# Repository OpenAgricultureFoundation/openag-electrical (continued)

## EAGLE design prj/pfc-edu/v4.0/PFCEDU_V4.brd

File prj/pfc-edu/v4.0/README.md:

## Electrical Design

Files here can be delivered to a contract manufacturer for PCB production. 

- BOM
- Gerber files
- PCB schematic (Eagle)
- PCB board (Eagle)

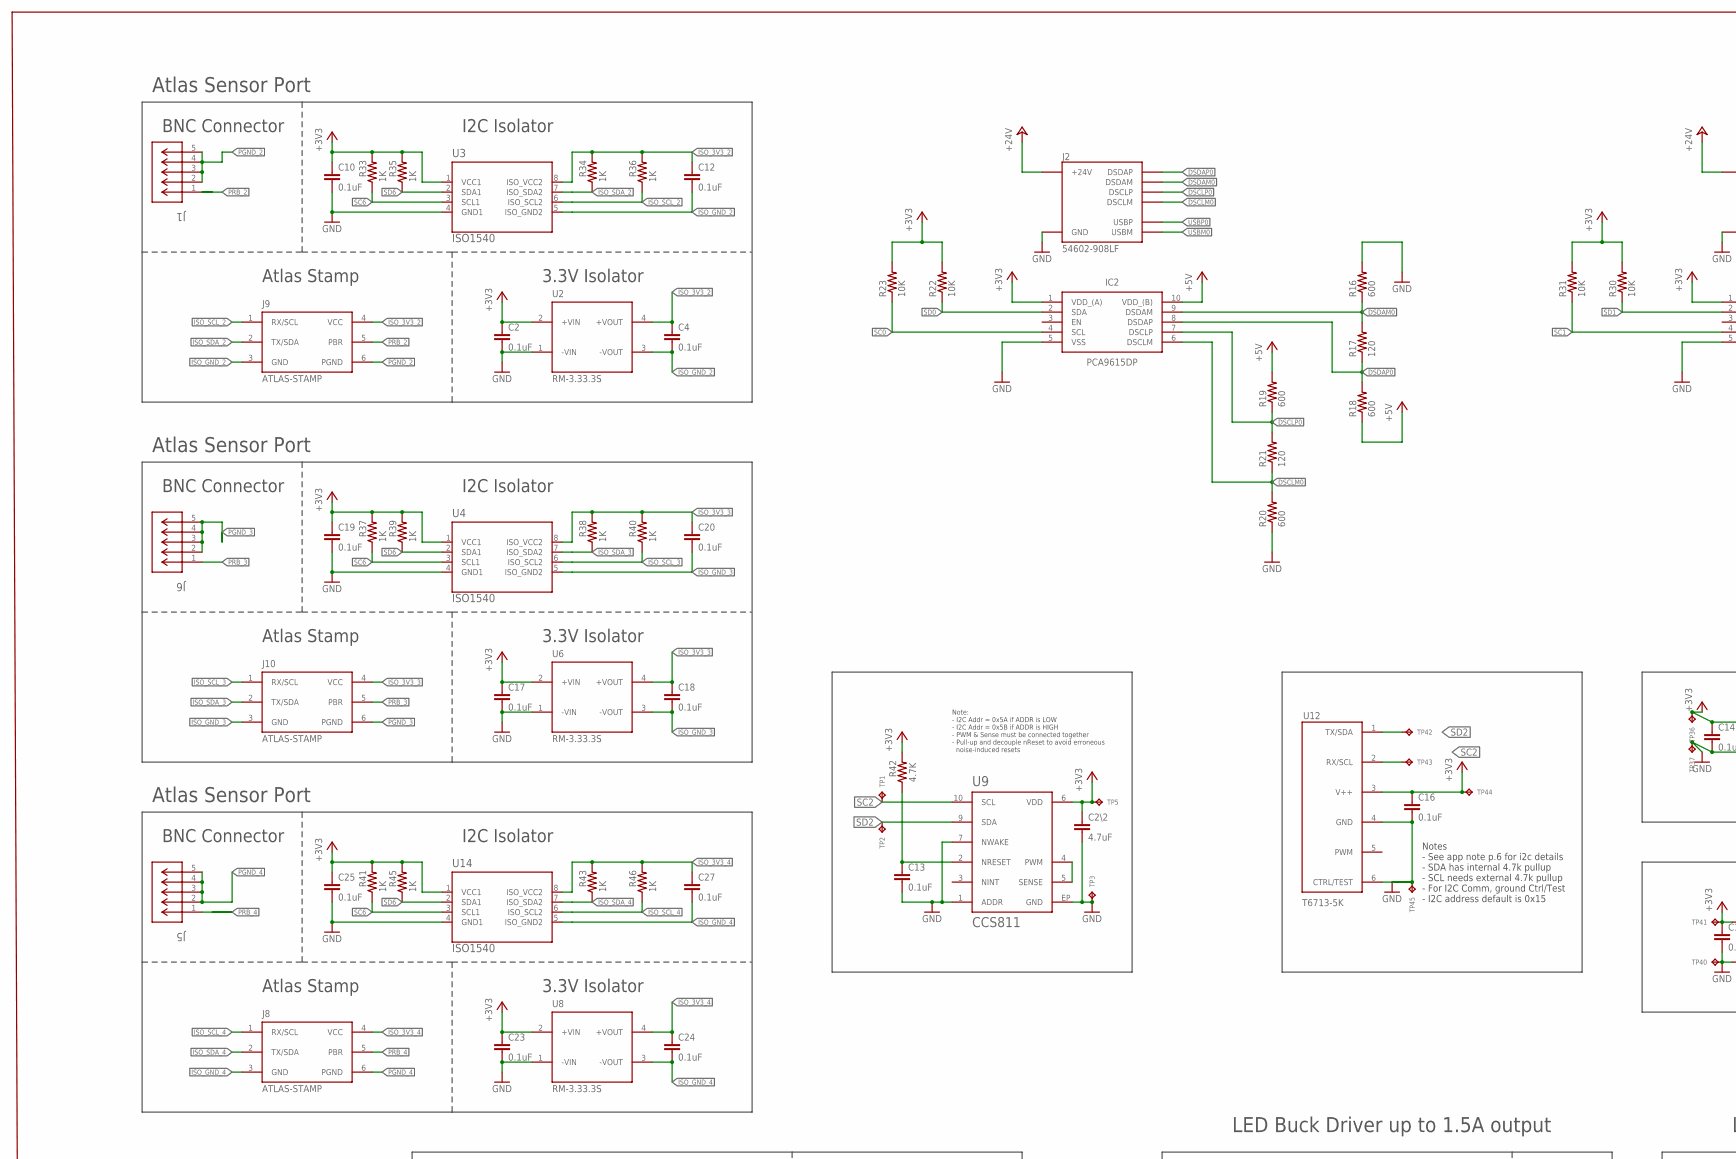
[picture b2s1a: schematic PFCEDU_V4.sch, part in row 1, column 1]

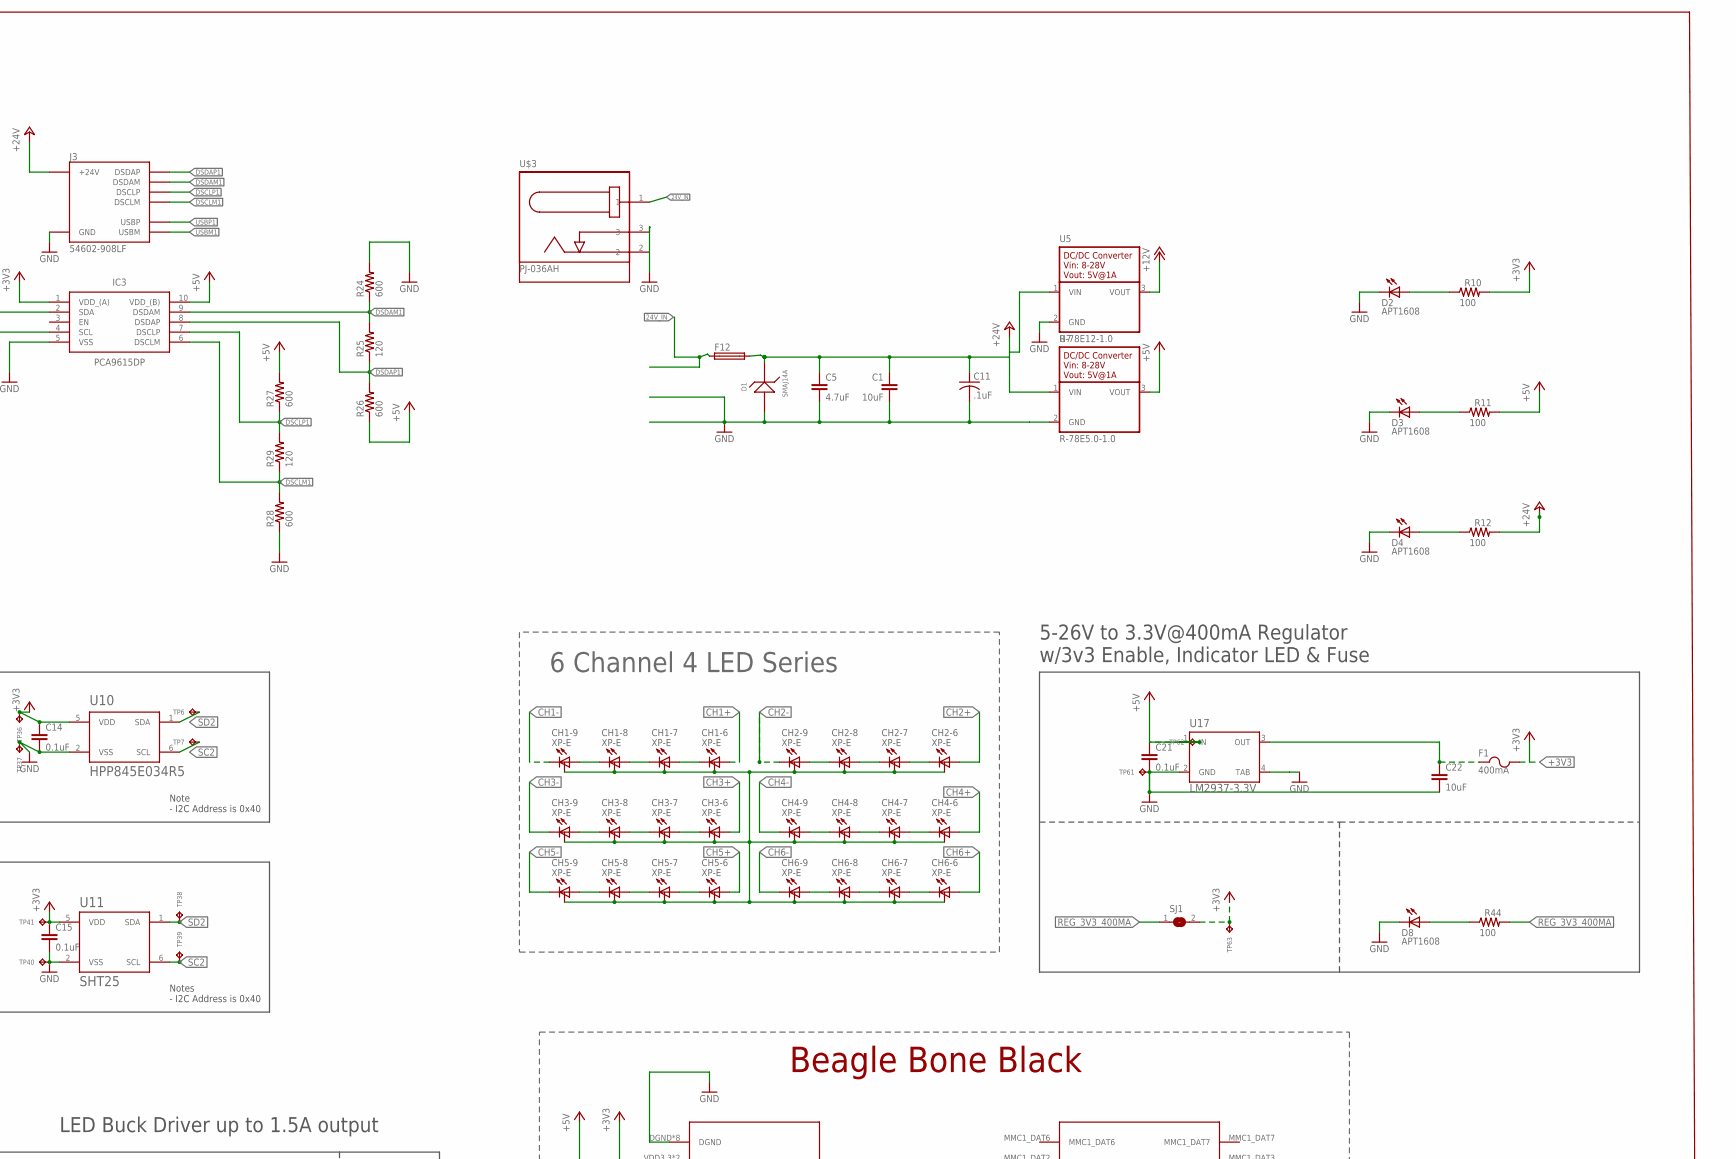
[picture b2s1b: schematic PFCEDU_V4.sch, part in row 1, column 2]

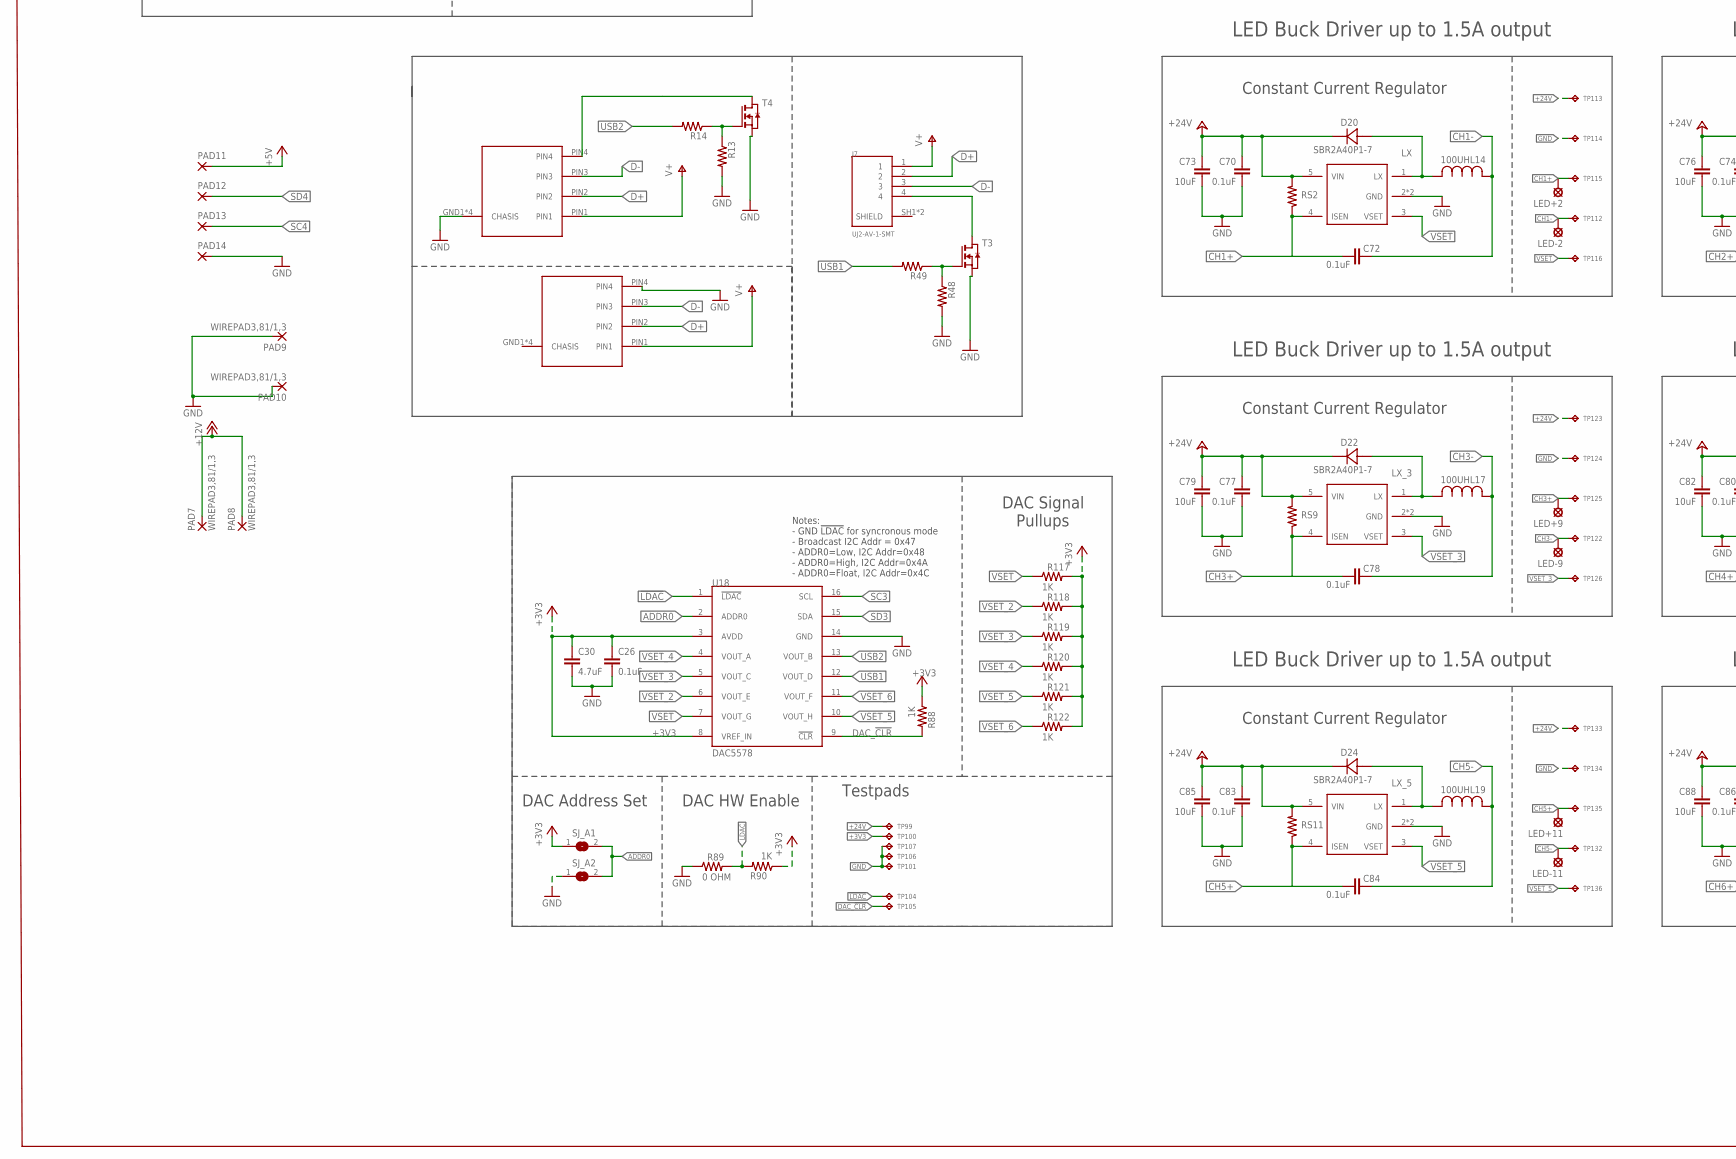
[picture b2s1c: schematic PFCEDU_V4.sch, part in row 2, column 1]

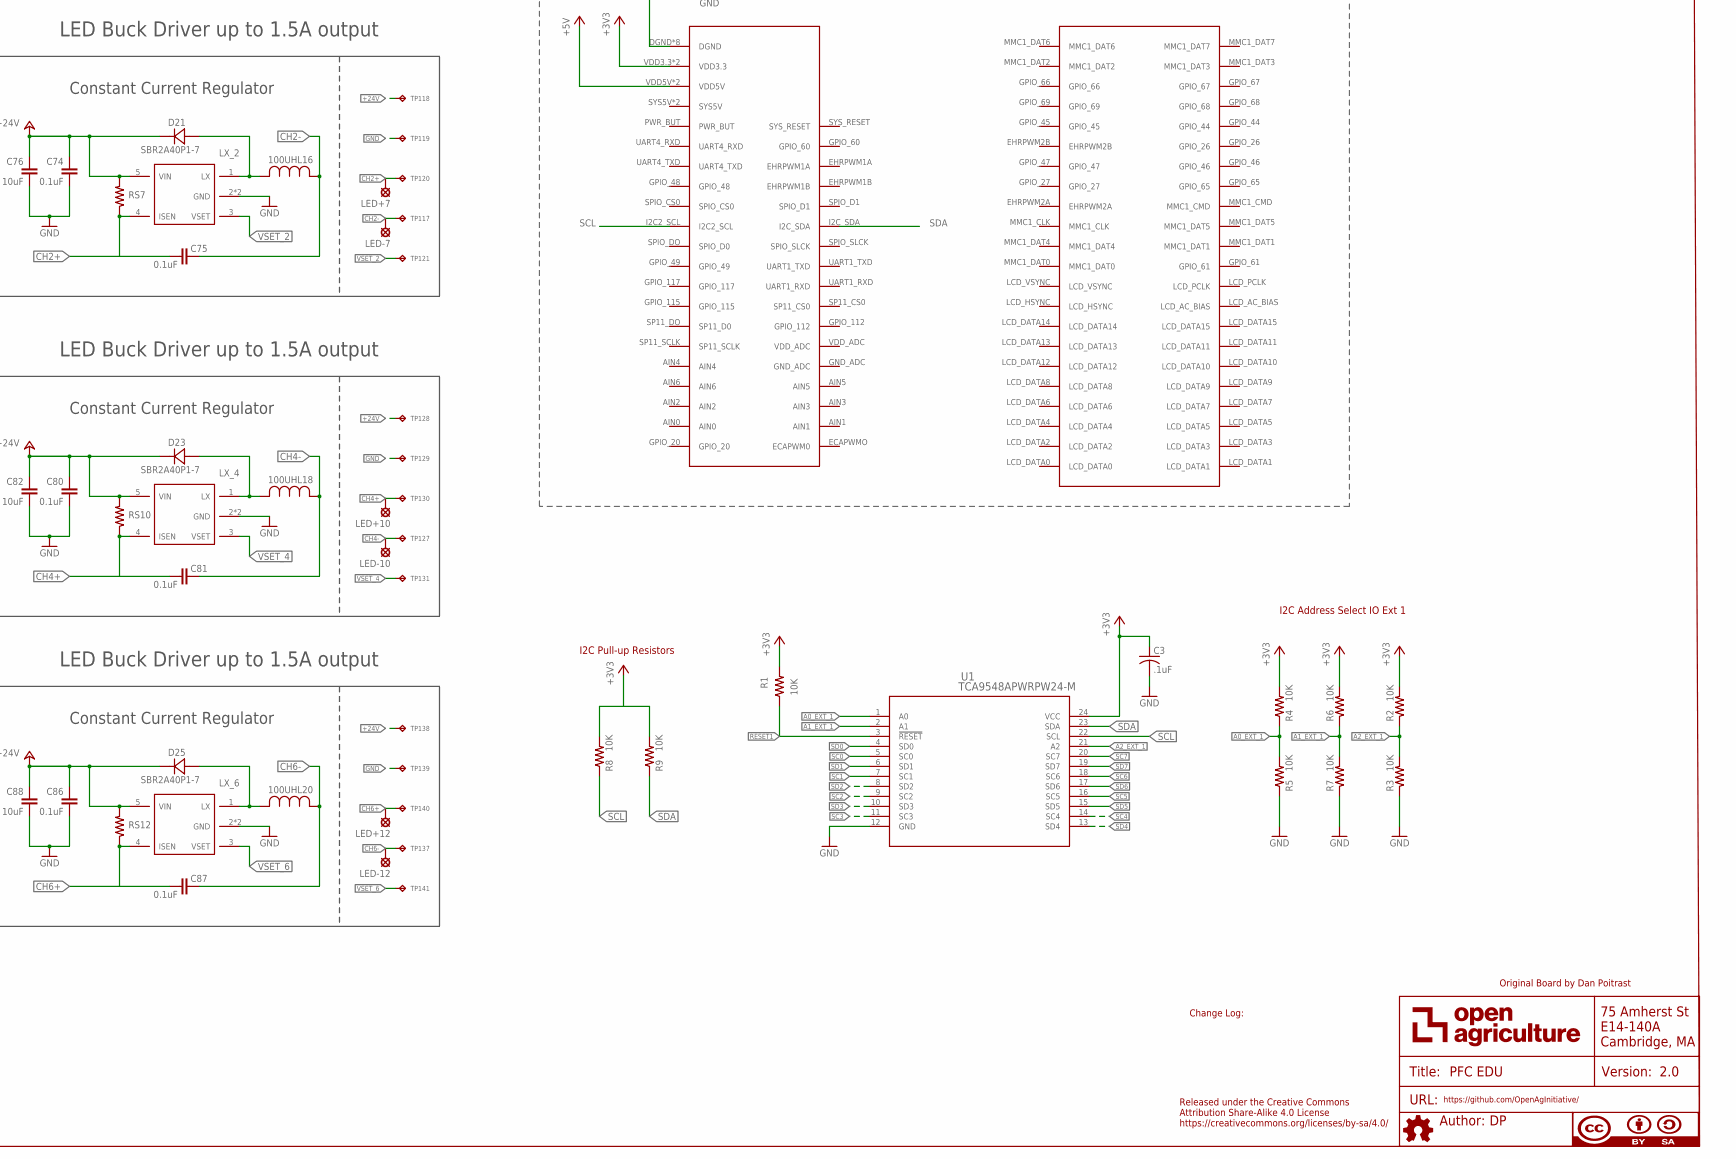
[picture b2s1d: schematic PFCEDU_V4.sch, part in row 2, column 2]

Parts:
ATTRIBUTES: DOCFIELD
C1, C22, C73, C76, C79, C82, C85, C88: 10uF; C0805
C2, C4, C10, C12, C13, C14, C15, C16, C17, C18, C19, C20, C21, C23, C24, C25, C26, C27, C70, C72, C74, C75, C77, C78, C80, C81, C83, C84, C86, C87: 0.1uF; C0603
C2\2, C5, C30: 4.7uF; C0805
C3, C11: .1uF; C0603@1
CH1-6, CH1-7, CH1-8, CH1-9, CH2-6, CH2-7, CH2-8, CH2-9, CH3-6, CH3-7, CH3-8, CH3-9, CH4-6, CH4-7, CH4-8, CH4-9, CH5-6, CH5-7, CH5-8, CH5-9, CH6-6, CH6-7, CH6-8, CH6-9: XP-E; CREE-XLAMP-XP-E
D1: SMAJ14A; DO-214AC
D2, D3, D4, D8: APT1608; CHIPLED_0603
D20, D21, D22, D23, D24, D25: SBR2A40P1-7; POWERDI123
F1: 400mA; 0603
F12: GSH15
IC2, IC3: PCA9615DP; SOP50P490X110-10N
J1, J5, J6: 5-1634503-1; CONN5_5-1634503-1
J2, J3: 54602-908LF; OPENAG-V1-RJ45
J7: UJ2-AV-1-SMT; CUI_UJ2-AV-1-SMT
J8, J9, J10: ATLAS-STAMP
L14, L16, L17, L18, L19, L20: 100UH; IND_BOURNS_SDR1307
LED+2, LED+7, LED+9, LED+10, LED+11, LED+12: SE14
LED-2, LED-7, LED-9, LED-10, LED-11, LED-12: SE14
PAD7, PAD8, PAD9, PAD10: WIREPAD3,81/1,3; 3,81/1,3
PAD11, PAD12, PAD13, PAD14: SMD2; SMD1,27-2,54
R1, R22, R23, R30, R31: 10K; R0603
R2, R3, R4, R5, R6, R7, R8, R9: 10K; 0603-RES
R10, R11, R12, R44: 100; RC0603N
R13, R14, R48, R49: R-US_R0805W; R0805W
R16, R18, R19, R20, R24, R26, R27, R28: 600; R0603
R17, R21, R25, R29: 120; R0603
R33, R34, R35, R36, R37, R38, R39, R40, R41, R43, R45, R46, R88, R90, R117, R118, R119, R120, R121, R122: 1K; RC0603N
R42: 4.7K; R1206
R89: 0 OHM; RC0603N
RS2, RS7, RS9, RS10, RS11, RS12: 6.34 ohm; R0805
SJ1: SOLDERJUMPERREFLOW_NOPASTE; SJ1
SJ_A1, SJ_A2: SOLDERJUMPERREFLOW_NOPASTE; SJ1
T3, T4: NMOSSOT23; SOT-23
TP1, TP2, TP3, TP5, TP6, TP7, TP36, TP37, TP38, TP39, TP40, TP41, TP42, TP43, TP44, TP45, TP61, TP62, TP63, TP112, TP113, TP114, TP115, TP116, TP117, TP118, TP119, TP120, TP121, TP122, TP123, TP124, TP125, TP126, TP127, TP128, TP129, TP130, TP131, TP132, TP133, TP134, TP135, TP136, TP137, TP138, TP139, TP140, TP141: TPTP06R; TP06R
TP99, TP100, TP101, TP104, TP105, TP106, TP107: TPTP04R; TP04R
U1: TCA9548APWRPW24-M; PW24-M
U2, U6, U8: RM-3.33.3S; RM3.33.3S-SIP4
U3, U4, U14: ISO1540; D8
U5: R-78E12-1.0; R-78E5.0-1.0
U7: R-78E5.0-1.0
U9: CCS811
U10: HPP845E034R5; HTU20D(F)
U11: SHT25; SHT2X
U12: T6713-5K; T6713
U17: LM2937-3.3V; MP04A
U18: DAC5578; TSSOP16
U$3: PJ-036AH; BARREL-JACK-PJ-036AH
U$4: BBB_SMD; 23PINHEADERSMD
U$5, U$6: USB_RIGHT
U$25, U$26, U$27, U$28, U$29, U$30: AL8861

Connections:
24V_IN: F12.1, U$3.1
!LDAC!: R89.2, R90.2, TP104.1, U18.1 (!LDAC!)
+3V3: C2.1, C2\2.1, C3.1, C10.1, C14.1, C15.1, C16.1, C17.1, C19.1, C23.1, C25.1, C26.1, C30.1, F1.2, IC2.1 (VDD_(A)), IC3.1 (VDD_(A)), R1.2, R2.2, R4.2, R6.2, R8.2, R9.2, R10.2, R22.2, R23.2, R30.2, R31.2, R33.2, R35.2, R37.2, R39.2, R41.2, R42.2, R45.2, R88.1, R90.1, R117.2, R118.2, R119.2, R120.2, R121.2, R122.2, SJ1.2, SJ_A1.1, TP5.TP, TP36.TP, TP41.TP, TP44.TP, TP63.TP, TP100.1, U1.24 (VCC), U2.2 (+VIN), U3.1 (VCC1), U4.1 (VCC1), U6.2 (+VIN), U8.2 (+VIN), U9.6 (VDD), U10.5 (VDD), U11.5 (VDD), U12.3 (V++), U14.1 (VCC1), U18.3 (AVDD), U18.8 (VREF_IN), U$4.VDD3.3, U$4.VDD3.31 (VDD3.3)
+5V: C21.1, IC2.10 (VDD_(B)), IC3.10 (VDD_(B)), PAD11.1, R11.2, R18.1, R19.2, R26.1, R27.2, TP62.TP, U7.3 (VOUT), U17.1 (IN), U$4.VDD5V, U$4.VDD5V1 (VDD5V)
+12V: PAD7.1, PAD8.1, U5.3 (VOUT)
+24V: C1.1, C5.1, C11.1, C70.1, C73.1, C74.1, C76.1, C77.1, C79.1, C80.1, C82.1, C83.1, C85.1, C86.1, C88.1, D1.C, D20.-, D21.-, D22.-, D23.-, D24.-, D25.-, F12.2, J2.24V(6) (+24V), J3.24V(6) (+24V), R12.2, RS2.2, RS7.2, RS9.2, RS10.2, RS11.2, RS12.2, TP99.1, TP113.TP, TP118.TP, TP123.TP, TP128.TP, TP133.TP, TP138.TP, U5.1 (VIN), U7.1 (VIN), U$25.5 (VIN), U$26.5 (VIN), U$27.5 (VIN), U$28.5 (VIN), U$29.5 (VIN), U$30.5 (VIN)
A0_EXT_1: R4.1, R5.2, U1.1 (A0)
A1_EXT_1: R6.1, R7.2, U1.2 (A1)
A2_EXT_1: R2.1, R3.2, U1.21 (A2)
ADDR0: SJ_A1.2, SJ_A2.2, U18.2 (ADDR0)
CH1+: C72.2, CH1-6.A, CH1-6.A@1 (A), LED+2.MP, RS2.1, TP115.TP, U$25.4 (ISEN)
CH1-: C72.1, CH1-9.C, CH1-9.C@1 (C), L14.2, LED-2.MP, TP112.TP
CH2+: C75.2, CH2-6.A, CH2-6.A@1 (A), LED+7.MP, RS7.1, TP120.TP, U$26.4 (ISEN)
CH2-: C75.1, CH2-9.C, CH2-9.C@1 (C), L16.2, LED-7.MP, TP117.TP
CH3+: C78.2, CH3-6.A, CH3-6.A@1 (A), LED+9.MP, RS9.1, TP125.TP, U$27.4 (ISEN)
CH3-: C78.1, CH3-9.C, CH3-9.C@1 (C), L17.2, LED-9.MP, TP122.TP
CH4+: C81.2, CH4-6.A, CH4-6.A@1 (A), LED+10.MP, RS10.1, TP130.TP, U$28.4 (ISEN)
CH4-: C81.1, CH4-9.C, CH4-9.C@1 (C), L18.2, LED-10.MP, TP127.TP
CH5+: C84.2, CH5-6.A, CH5-6.A@1 (A), LED+11.MP, RS11.1, TP135.TP, U$29.4 (ISEN)
CH5-: C84.1, CH5-9.C, CH5-9.C@1 (C), L19.2, LED-11.MP, TP132.TP
CH6+: C87.2, CH6-6.A, CH6-6.A@1 (A), LED+12.MP, RS12.1, TP140.TP, U$30.4 (ISEN)
CH6-: C87.1, CH6-9.C, CH6-9.C@1 (C), L20.2, LED-12.MP, TP137.TP
D+: J7.2, U$5.PIN2, U$6.PIN2
D-: J7.3, U$5.PIN3, U$6.PIN3
DAC_!CLR!: R88.2, TP105.1, U18.9 (!CLR!)
DSCLM0: IC2.6 (DSCLM), J2.DSCLM(5) (DSCLM), R20.2, R21.1
DSCLM1: IC3.6 (DSCLM), J3.DSCLM(5) (DSCLM), R28.2, R29.1
DSCLP0: IC2.7 (DSCLP), J2.DSCLP(4) (DSCLP), R19.1, R21.2
DSCLP1: IC3.7 (DSCLP), J3.DSCLP(4) (DSCLP), R27.1, R29.2
DSDAM0: IC2.9 (DSDAM), J2.DSDAM(2) (DSDAM), R16.1, R17.2
DSDAM1: IC3.9 (DSDAM), J3.DSDAM(2) (DSDAM), R24.1, R25.2
DSDAP0: IC2.8 (DSDAP), J2.DSDAP(1) (DSDAP), R17.1, R18.2
DSDAP1: IC3.8 (DSDAP), J3.DSDAP(1) (DSDAP), R25.1, R26.2
GND: C1.2, C2.2, C2\2.2, C3.2, C5.2, C10.2, C11.2, C13.2, C14.2, C15.2, C16.2, C17.2, C19.2, C21.2, C22.2, C23.2, C25.2, C26.2, C30.2, C70.2, C73.2, C74.2, C76.2, C77.2, C79.2, C80.2, C82.2, C83.2, C85.2, C86.2, C88.2, D1.A, D2.C, D3.C, D4.C, D8.C, IC2.5 (VSS), IC3.5 (VSS), J2.GND(3) (GND), J3.GND(3) (GND), PAD9.1, PAD10.1, PAD14.1, R3.1, R5.1, R7.1, R13.2, R16.2, R20.1, R24.2, R28.1, R48.2, R89.1, SJ_A2.1, T3.2 (S), T4.2 (S), TP3.TP, TP37.TP, TP40.TP, TP45.TP, TP61.TP, TP101.1, TP106.1, TP107.1, TP114.TP, TP119.TP, TP124.TP, TP129.TP, TP134.TP, TP139.TP, U1.12 (GND), U2.1 (-VIN), U3.4 (GND1), U4.4 (GND1), U5.2 (GND), U6.1 (-VIN), U7.2 (GND), U8.1 (-VIN), U9.1 (ADDR), U9.7 (NWAKE), U9.EP (GND), U10.2 (VSS), U11.2 (VSS), U12.4 (GND), U12.6 (CTRL/TEST), U14.4 (GND1), U17.2 (GND), U17.4 (TAB), U18.14 (GND), U$3.2, U$3.3, U$4.DGND, U$4.DGND1 (DGND), U$4.DGND2 (DGND), U$4.DGND3 (DGND), U$4.DGND4 (DGND), U$4.DGND5 (DGND), U$4.DGND6 (DGND), U$4.DGND7 (DGND), U$5.GND1 (CHASIS), U$5.GND2 (CHASIS), U$5.GND3 (CHASIS), U$5.GND4 (CHASIS), U$6.PIN4, U$25.2 (GND), U$25.44 (GND), U$26.2 (GND), U$26.44 (GND), U$27.2 (GND), U$27.44 (GND), U$28.2 (GND), U$28.44 (GND), U$29.2 (GND), U$29.44 (GND), U$30.2 (GND), U$30.44 (GND)
ISO_3V3_2: C4.1, C12.1, J9.4 (VCC), R34.2, R36.2, U2.4 (+VOUT), U3.8 (ISO_VCC2)
ISO_3V3_3: C18.1, C20.1, J10.4 (VCC), R38.2, R40.2, U4.8 (ISO_VCC2), U6.4 (+VOUT)
ISO_3V3_4: C24.1, C27.1, J8.4 (VCC), R43.2, R46.2, U8.4 (+VOUT), U14.8 (ISO_VCC2)
ISO_GND_2: C4.2, C12.2, J9.3 (GND), U2.3 (-VOUT), U3.5 (ISO_GND2)
ISO_GND_3: C18.2, C20.2, J10.3 (GND), U4.5 (ISO_GND2), U6.3 (-VOUT)
ISO_GND_4: C24.2, C27.2, J8.3 (GND), U8.3 (-VOUT), U14.5 (ISO_GND2)
ISO_SCL_2: J9.1 (RX/SCL), R36.1, U3.6 (ISO_SCL2)
ISO_SCL_3: J10.1 (RX/SCL), R40.1, U4.6 (ISO_SCL2)
ISO_SCL_4: J8.1 (RX/SCL), R46.1, U14.6 (ISO_SCL2)
ISO_SDA_2: J9.2 (TX/SDA), R34.1, U3.7 (ISO_SDA2)
ISO_SDA_3: J10.2 (TX/SDA), R38.1, U4.7 (ISO_SDA2)
ISO_SDA_4: J8.2 (TX/SDA), R43.1, U14.7 (ISO_SDA2)
LX: D20.+, L14.1, U$25.1 (LX)
LX_2: D21.+, L16.1, U$26.1 (LX)
LX_3: D22.+, L17.1, U$27.1 (LX)
LX_4: D23.+, L18.1, U$28.1 (LX)
LX_5: D24.+, L19.1, U$29.1 (LX)
LX_6: D25.+, L20.1, U$30.1 (LX)
unnamed: R13.1, R14.1, T4.3 (G)
unnamed: D3.A, R11.1
unnamed: R48.1, R49.1, T3.3 (G)
unnamed: D4.A, R12.1
unnamed: J7.4, T3.1 (D)
unnamed: T4.1 (D), U$5.PIN4
unnamed: D2.A, R10.1
unnamed: CH2-8.C, CH2-8.C@1 (C), CH2-9.A, CH2-9.A@1 (A)
unnamed: CH2-7.C, CH2-7.C@1 (C), CH2-8.A, CH2-8.A@1 (A)
unnamed: CH2-6.C, CH2-6.C@1 (C), CH2-7.A, CH2-7.A@1 (A)
unnamed: CH4-8.C, CH4-8.C@1 (C), CH4-9.A, CH4-9.A@1 (A)
unnamed: CH4-7.C, CH4-7.C@1 (C), CH4-8.A, CH4-8.A@1 (A)
unnamed: CH4-6.C, CH4-6.C@1 (C), CH4-7.A, CH4-7.A@1 (A)
unnamed: CH6-8.C, CH6-8.C@1 (C), CH6-9.A, CH6-9.A@1 (A)
unnamed: CH6-7.C, CH6-7.C@1 (C), CH6-8.A, CH6-8.A@1 (A)
unnamed: U9.4 (PWM), U9.5 (SENSE)
unnamed: C13.1, R42.1, U9.2 (NRESET)
unnamed: CH6-6.C, CH6-6.C@1 (C), CH6-7.A, CH6-7.A@1 (A)
unnamed: CH1-8.C, CH1-8.C@1 (C), CH1-9.A, CH1-9.A@1 (A)
unnamed: CH1-7.C, CH1-7.C@1 (C), CH1-8.A, CH1-8.A@1 (A)
unnamed: CH1-6.C, CH1-6.C@1 (C), CH1-7.A, CH1-7.A@1 (A)
unnamed: CH3-8.C, CH3-8.C@1 (C), CH3-9.A, CH3-9.A@1 (A)
unnamed: CH3-7.C, CH3-7.C@1 (C), CH3-8.A, CH3-8.A@1 (A)
unnamed: CH3-6.C, CH3-6.C@1 (C), CH3-7.A, CH3-7.A@1 (A)
unnamed: CH5-8.C, CH5-8.C@1 (C), CH5-9.A, CH5-9.A@1 (A)
unnamed: CH5-7.C, CH5-7.C@1 (C), CH5-8.A, CH5-8.A@1 (A)
unnamed: CH5-6.C, CH5-6.C@1 (C), CH5-7.A, CH5-7.A@1 (A)
unnamed: D8.A, R44.1
unnamed: C22.1, F1.1, U17.3 (OUT)
PGND_2: J1.2, J1.3, J1.4, J1.5, J9.6 (PGND)
PGND_3: J6.2, J6.3, J6.4, J6.5, J10.6 (PGND)
PGND_4: J5.2, J5.3, J5.4, J5.5, J8.6 (PGND)
PRB_2: J1.1, J9.5 (PBR)
PRB_3: J6.1, J10.5 (PBR)
PRB_4: J5.1, J8.5 (PBR)
REG_3V3_400MA: R44.2, SJ1.1
RESET1: R1.1, U1.3 (!RESET)
SC0: IC2.4 (SCL), R23.1, U1.5 (SC0)
SC1: IC3.4 (SCL), R31.1, U1.7 (SC1)
SC2: TP1.TP, TP7.TP, TP39.TP, TP43.TP, U1.9 (SC2), U9.10 (SCL), U10.6 (SCL), U11.6 (SCL), U12.2 (RX/SCL)
SC3: U1.11 (SC3), U18.16 (SCL)
SC4: PAD13.1, U1.14 (SC4)
SC5: U1.16 (SC5)
SC6: R33.1, R37.1, R41.1, U1.18 (SC6), U3.3 (SCL1), U4.3 (SCL1), U14.3 (SCL1)
SC7: U1.20 (SC7)
SCL: R8.1, U1.22 (SCL), U$4.I2C2_SCL
SD0: IC2.2 (SDA), R22.1, U1.4 (SD0)
SD1: IC3.2 (SDA), R30.1, U1.6 (SD1)
SD2: TP2.TP, TP6.TP, TP38.TP, TP42.TP, U1.8 (SD2), U9.9 (SDA), U10.1 (SDA), U11.1 (SDA), U12.1 (TX/SDA)
SD3: U1.10 (SD3), U18.15 (SDA)
SD4: PAD12.1, U1.13 (SD4)
SD5: U1.15 (SD5)
SD6: R35.1, R39.1, R45.1, U1.17 (SD6), U3.2 (SDA1), U4.2 (SDA1), U14.2 (SDA1)
SD7: U1.19 (SD7)
SDA: R9.1, U1.23 (SDA), U$4.I2C_SDA
T1: CH1-6.THERM, CH1-7.THERM, CH1-8.THERM, CH1-9.THERM, CH2-6.THERM, CH2-7.THERM, CH2-8.THERM, CH2-9.THERM, CH3-6.THERM, CH3-7.THERM, CH3-8.THERM, CH3-9.THERM, CH4-6.THERM, CH4-7.THERM, CH4-8.THERM, CH4-9.THERM, CH5-6.THERM, CH5-7.THERM, CH5-8.THERM, CH5-9.THERM, CH6-6.THERM, CH6-7.THERM, CH6-8.THERM, CH6-9.THERM
USB1: R49.2, U18.12 (VOUT_D)
USB2: R14.2, U18.13 (VOUT_B)
USBM0: J2.USBM(8) (USBM)
USBM1: J3.USBM(8) (USBM)
USBP0: J2.USBP(7) (USBP)
USBP1: J3.USBP(7) (USBP)
V+: J7.1, U$5.PIN1, U$6.PIN1
VSET: R117.1, TP116.TP, U18.7 (VOUT_G), U$25.3 (VSET)
VSET_2: R118.1, TP121.TP, U18.6 (VOUT_E), U$26.3 (VSET)
VSET_3: R119.1, TP126.TP, U18.5 (VOUT_C), U$27.3 (VSET)
VSET_4: R120.1, TP131.TP, U18.4 (VOUT_A), U$28.3 (VSET)
VSET_5: R121.1, TP136.TP, U18.10 (VOUT_H), U$29.3 (VSET)
VSET_6: R122.1, TP141.TP, U18.11 (VOUT_F), U$30.3 (VSET)

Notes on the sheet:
Original Board by Dan Poitrast
Change Log:
I2C Pull-up Resistors
Released under the Creative Commons Attribution Share-Alike 4.0 License https://creativecommons.org/licenses/by-sa/4.0/
I2C Address Select IO Ext 1
Note: - I2C Addr = 0x5A if ADDR is LOW - I2C Addr = 0x5B if ADDR is HIGH - PWM & Sense must be connected together - Pull-up and decouple nReset to avoid erroneous noise-induced resets
Note - I2C Address is 0x40
Notes - I2C Address is 0x40
Notes - See app note p.6 for i2c details - SDA has internal 4.7k pullup - SCL needs external 4.7k pullup - For I2C Comm, ground Ctrl/Test - I2C address default is 0x15
6 Channel 4 LED Series
5-26V to 3.3V@400mA Regulator w/3v3 Enable, Indicator LED & Fuse
Notes: - GND !LDAC! for syncronous mode - Broadcast I2C Addr = 0x47 - ADDR0=Low, I2C Addr=0x48 - ADDR0=High, I2C Addr=0x4A - ADDR0=Float, I2C Addr=0x4C
Testpads
DAC Signal Pullups
DAC Address Set
DAC HW Enable
LED Buck Driver up to 1.5A output
Constant Current Regulator
3.3V Isolator
I2C Isolator
Atlas Stamp
BNC Connector
Atlas Sensor Port

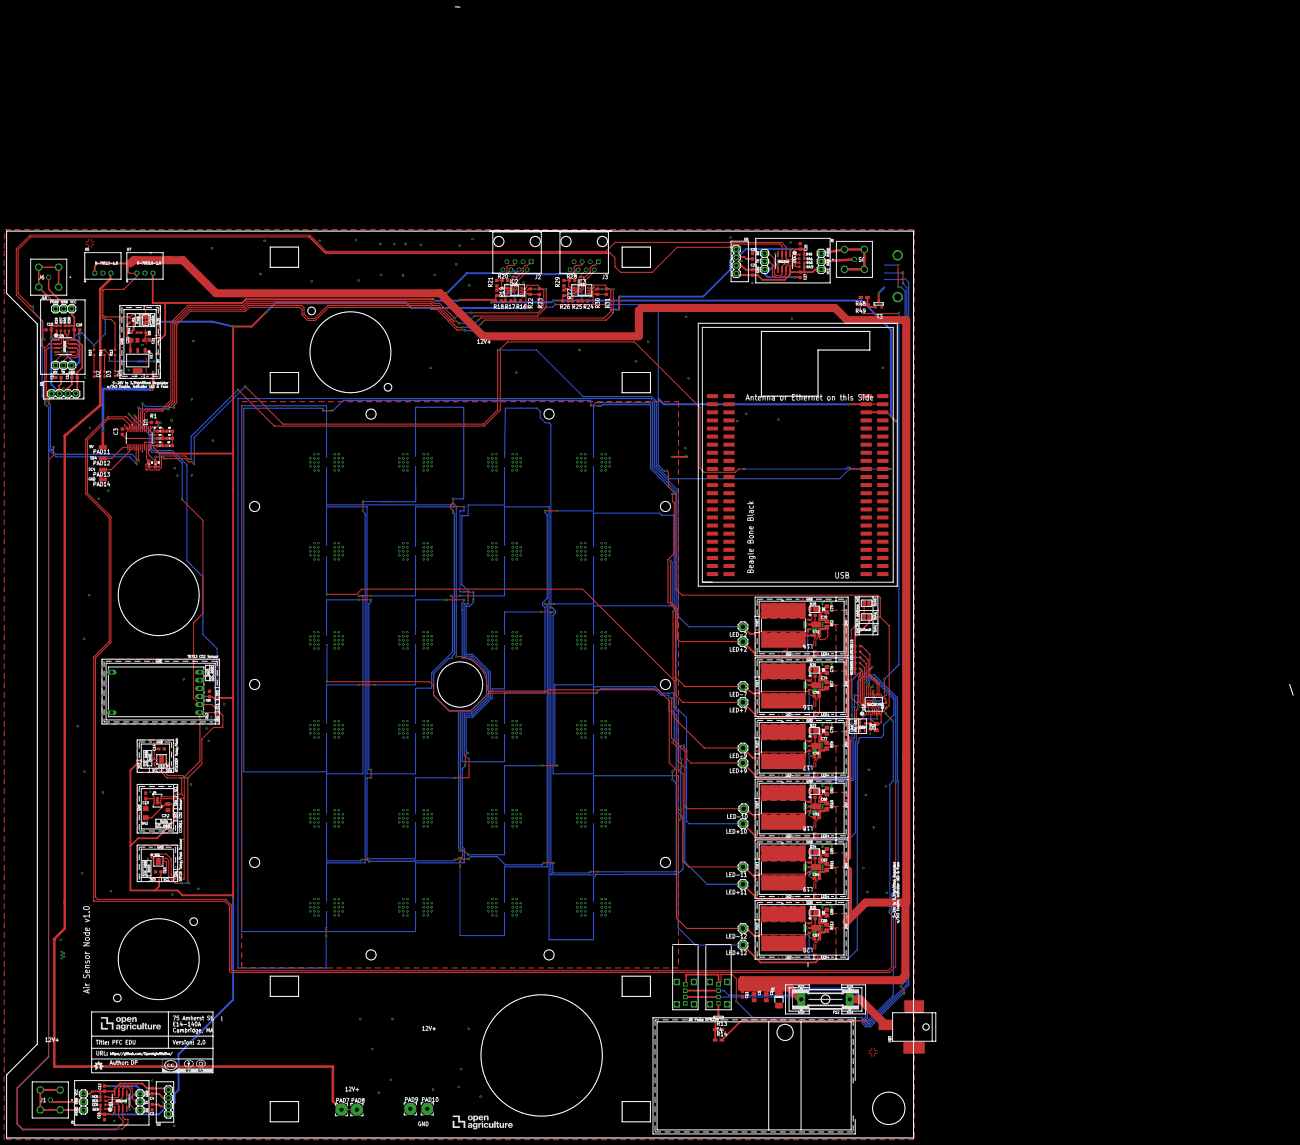
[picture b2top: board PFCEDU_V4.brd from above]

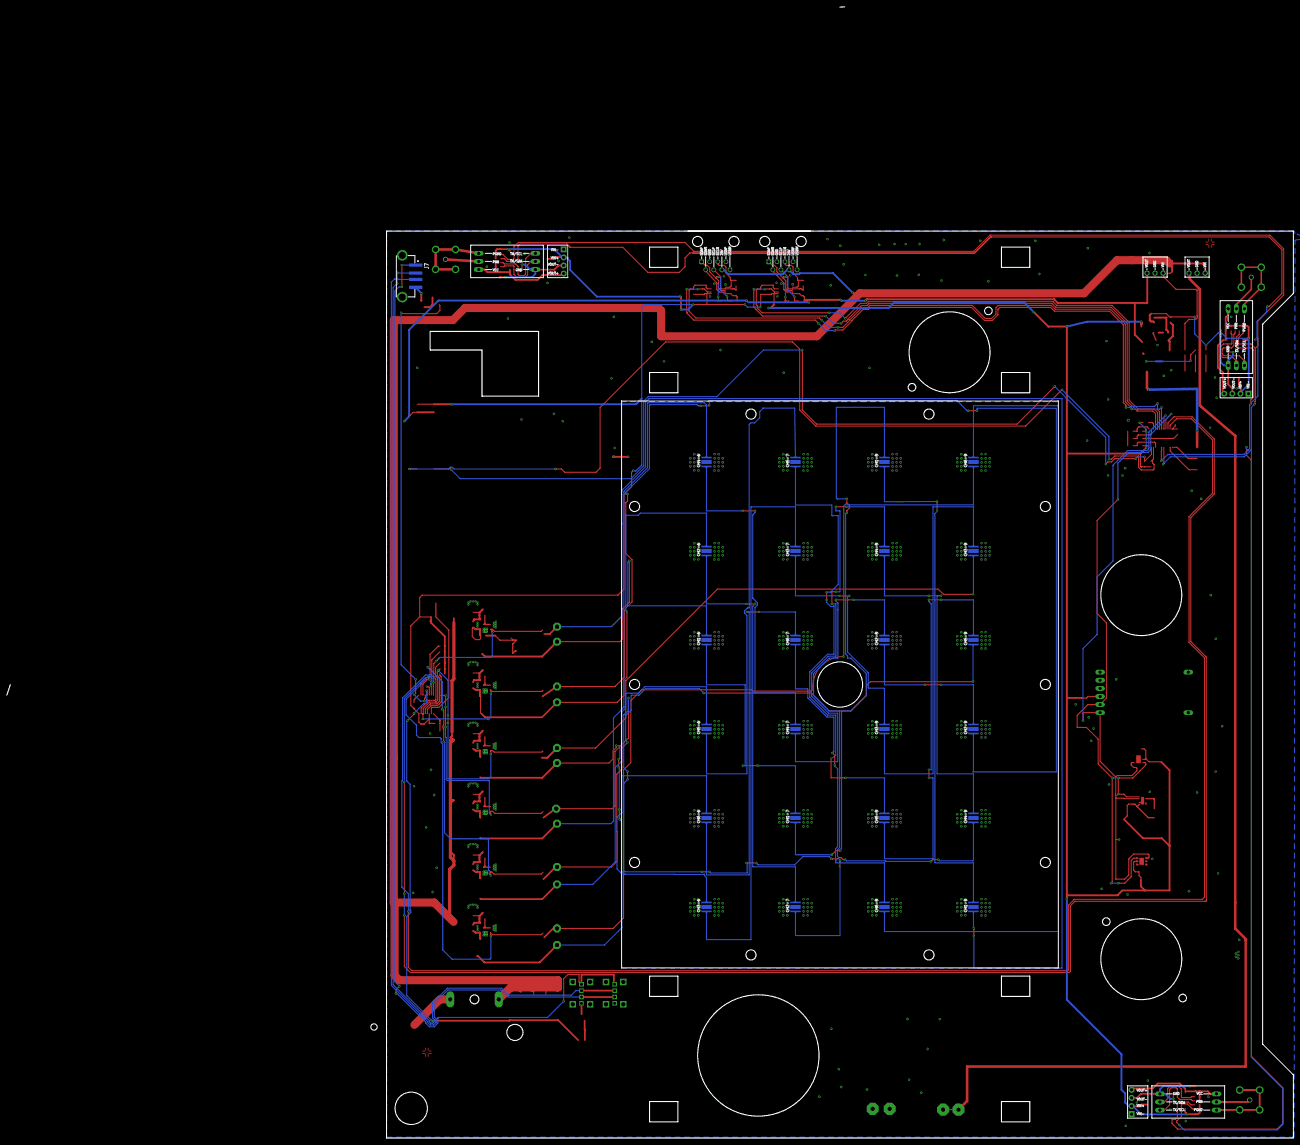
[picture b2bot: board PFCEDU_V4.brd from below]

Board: 2 copper layers, 284.7 x 284.7 mm, 268 parts (25 on the bottom side), 113 nets.

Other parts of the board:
U$1, U$2: PASSER-CIRCLE
U$9: OPENAG-LOGO-750-MIL

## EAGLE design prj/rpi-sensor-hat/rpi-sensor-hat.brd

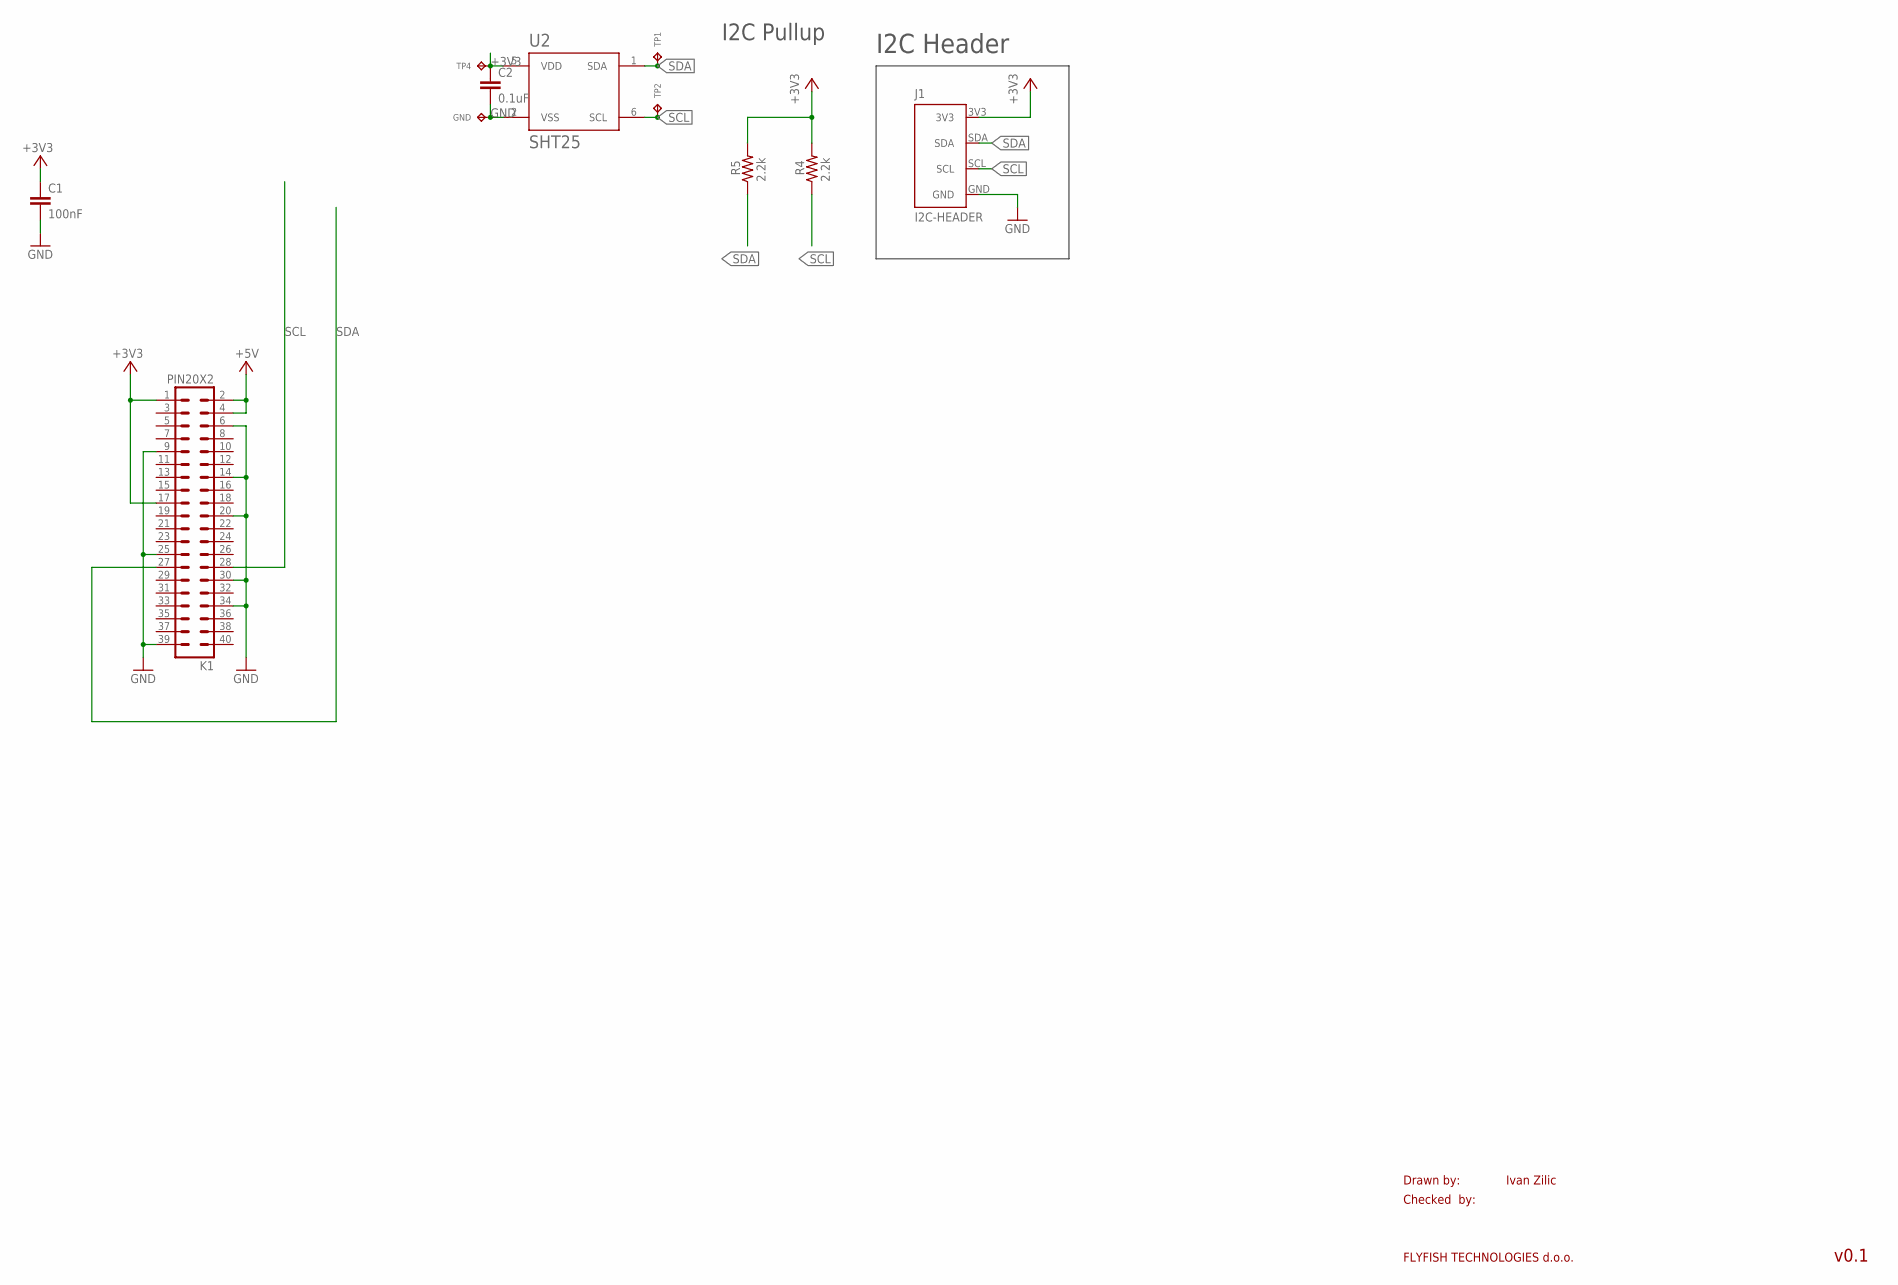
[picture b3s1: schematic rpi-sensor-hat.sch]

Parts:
C1: 100nF; C0805K
C2: 0.1uF; C0603
GND: TPTP06R; TP06R
J1: I2C-HEADER; HEADER-I2C
K1: PIN20X2; PIN_20X2
R4, R5: 2.2k; RC0603N
TP1, TP2, TP4: TPTP06R; TP06R
U2: SHT25; SHT2X

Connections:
+3V3: C1.1, C2.1, J1.3V3, K1.1, K1.17, R4.2, R5.2, TP4.TP, U2.5 (VDD)
+5V: K1.2, K1.4
GND: C1.2, C2.2, GND.TP, J1.GND, K1.6, K1.9, K1.14, K1.20, K1.25, K1.30, K1.34, K1.39, U2.2 (VSS)
SCL: J1.SCL, K1.28, R4.1, TP2.TP, U2.6 (SCL)
SDA: J1.SDA, K1.27, R5.1, TP1.TP, U2.1 (SDA)

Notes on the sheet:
Drawn by:
Checked by:
FLYFISH TECHNOLOGIES d.o.o.
Ivan Zilic
v0.1
I2C Pullup
I2C Header

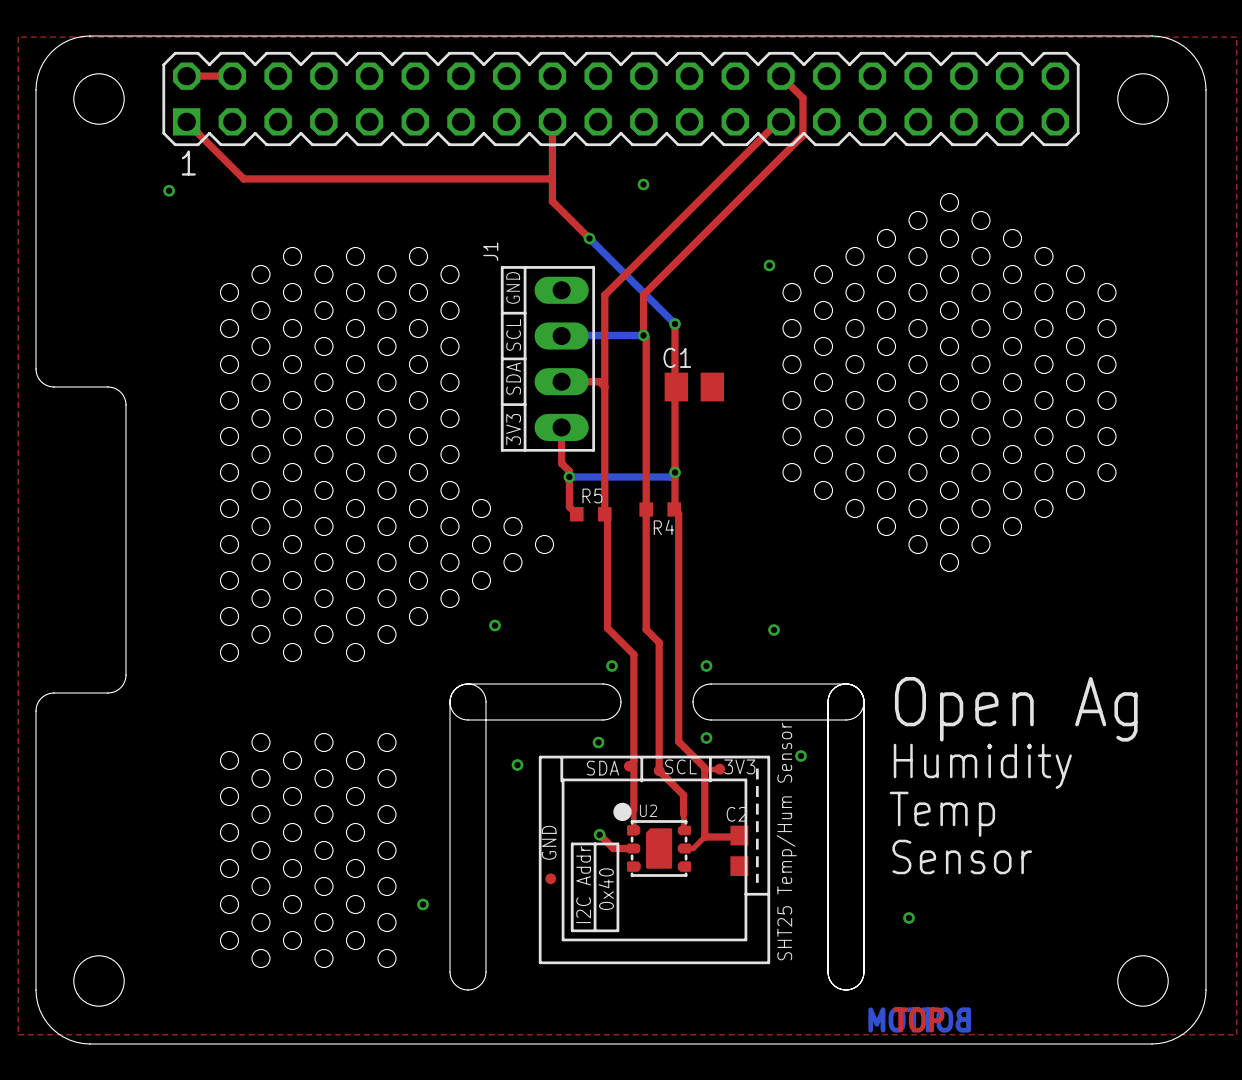
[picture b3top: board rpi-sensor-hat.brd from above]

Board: 2 copper layers, 65.0 x 56.0 mm, 11 parts (0 on the bottom side), 5 nets.
